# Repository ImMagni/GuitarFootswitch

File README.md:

# GuitarFootswitch
<br>
A simple footswitch designed to change channels and toggle modes on analog and digital guitar amplifiers.
Compatible with most amps that use TS jack switching. i also added a rgb led that shows the state of the switch(red and green)
## BOM
- 1/4 TS jack
- Wires
- dpdt switch
- Metal box/ 3d case
- RGB led
- SPST switch
- Battery holder 2x AAA

## Video

https://www.youtube.com/watch?v=f8zoFo4aWhc
  
Case|Schematic|Pcb
:-:|:-:|:-:|
||

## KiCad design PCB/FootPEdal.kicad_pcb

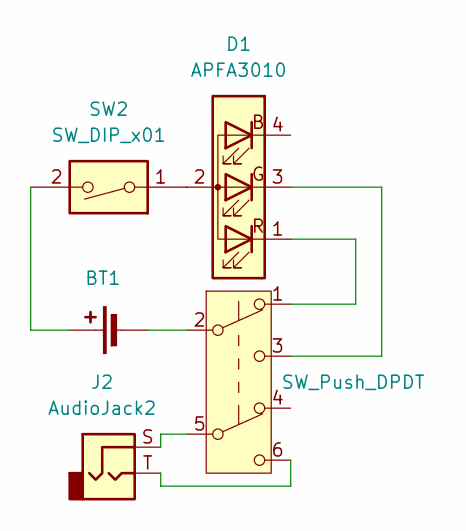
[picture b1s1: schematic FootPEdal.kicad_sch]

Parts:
BT1: Battery_Cell; BatteryHolder_Keystone_2468_2xAAA
D1: APFA3010; LED_D5.0mm-4_RGB
J2: AudioJack2; Jack_6.35mm_Neutrik_NMJ6HFD2-AU_Horizontal
SW1: SW_Push_DPDT; SW_PUSH_E-Switch_FS5700DP_DPDT
SW2: SW_DIP_x01; SW_SPST_Omron_B3F-50xx

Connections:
unnamed: BT1.1 (+), SW2.2
unnamed: BT1.2 (-), SW1.2 (B)
unnamed: D1.2 (A), SW2.1
unnamed: D1.3 (G), SW1.3 (C)
unnamed: D1.1 (R), SW1.1 (A)
unnamed: J2.S, SW1.5 (B)
unnamed: J2.T, SW1.6 (C)

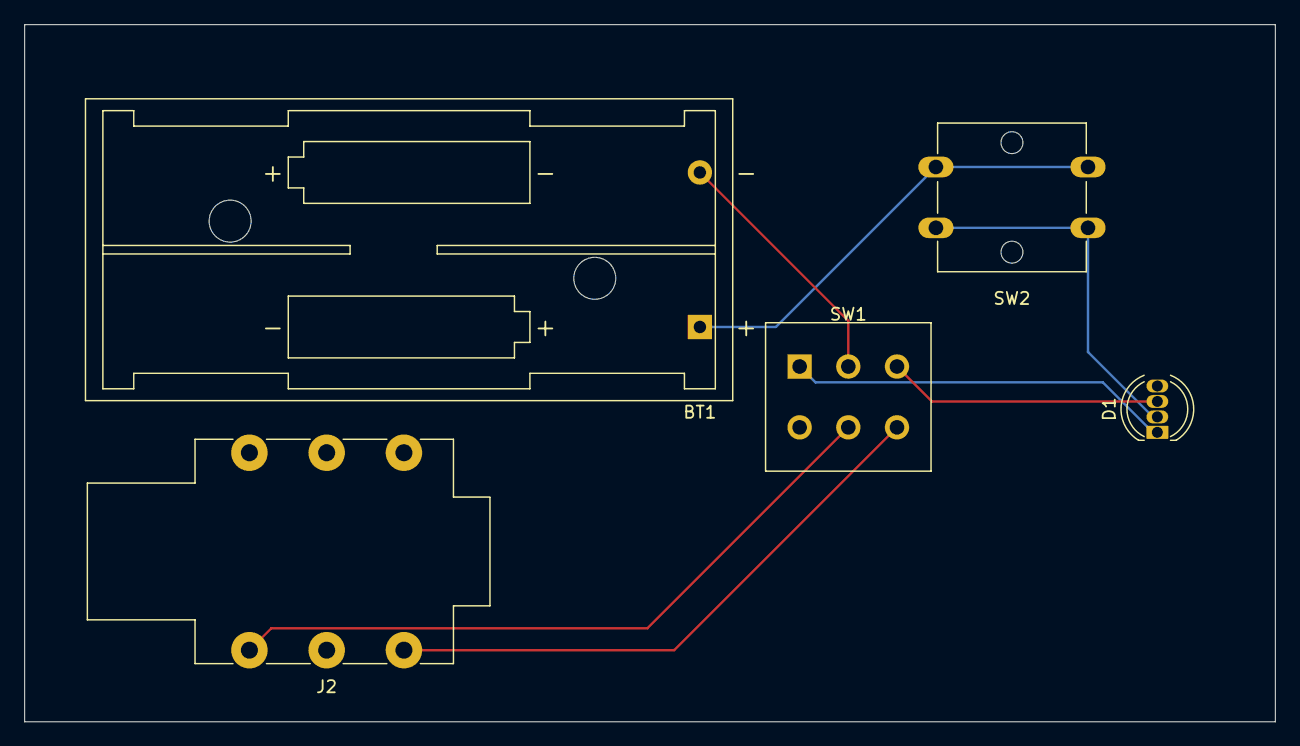
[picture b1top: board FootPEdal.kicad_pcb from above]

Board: 2 copper layers, 102.8 x 57.3 mm, 5 parts (0 on the bottom side), 7 nets.

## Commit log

2025-12-09 Rename model render.png to modelrender.png
2026-01-07 Update README with corrected item names and video link
